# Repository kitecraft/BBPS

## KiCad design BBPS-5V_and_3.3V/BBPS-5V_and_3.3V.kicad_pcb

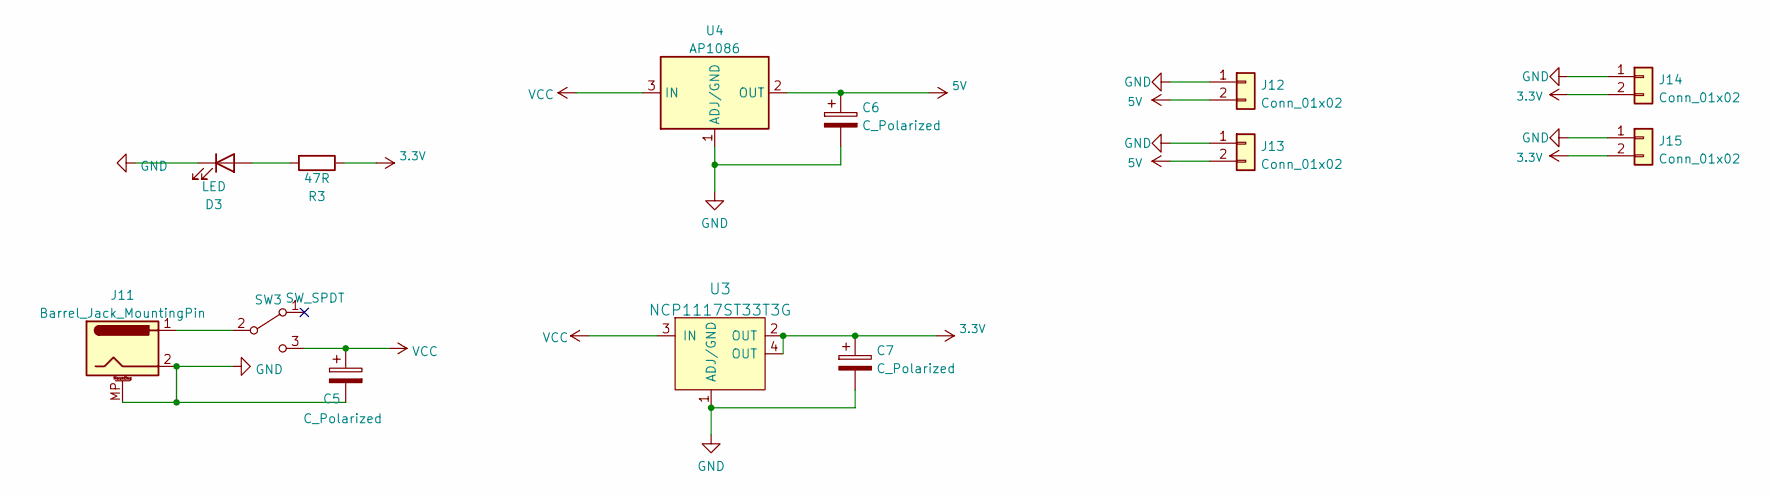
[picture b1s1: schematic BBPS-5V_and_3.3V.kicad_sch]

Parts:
C5: C_Polarized; CP_Elec_6.3x5.9
C6, C7: C_Polarized; C_0805_2012Metric
D3: LED; LED_1206_3216Metric
J11: Barrel_Jack_MountingPin; BarrelJack_CUI_PJ-102AH_Horizontal_3_Pin_Short
J12, J13, J14, J15: Conn_01x02; PinHeader_1x02_P2.54mm_Vertical
R3: 47R; R_1206_3216Metric
SW3: SW_SPDT; SPDT_Switch_3mm
U3: NCP1117ST33T3G; SOT-223; MPN NCP1117ST33T3G; Digi-Key_PN NCP1117ST33T3GOSCT-ND
U4: AP1086; TO-263-2

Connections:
3.3V: C7.1, J14.2, J15.2, R3.1, U3.2 (OUT), U3.4 (OUT)
5V: C6.1, J12.2, J13.2, U4.2 (OUT)
GND: C5.2, C6.2, C7.2, D3.1 (K), J11.2, J11.MP (MountPin), J12.1, J13.1, J14.1, J15.1, U3.1 (ADJ/GND), U4.1 (ADJ/GND)
unnamed: D3.2 (A), R3.2
unnamed: J11.1, SW3.2 (B)
VCC: C5.1, SW3.3 (C), U3.3 (IN), U4.3 (IN)

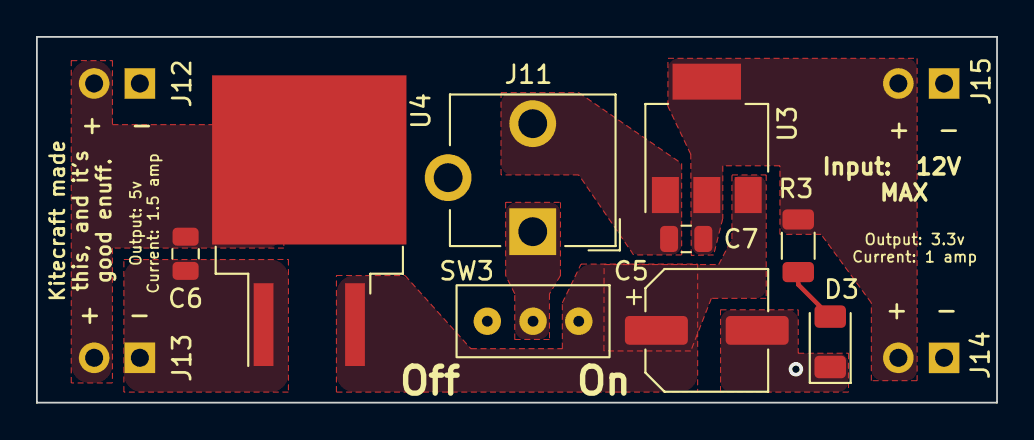
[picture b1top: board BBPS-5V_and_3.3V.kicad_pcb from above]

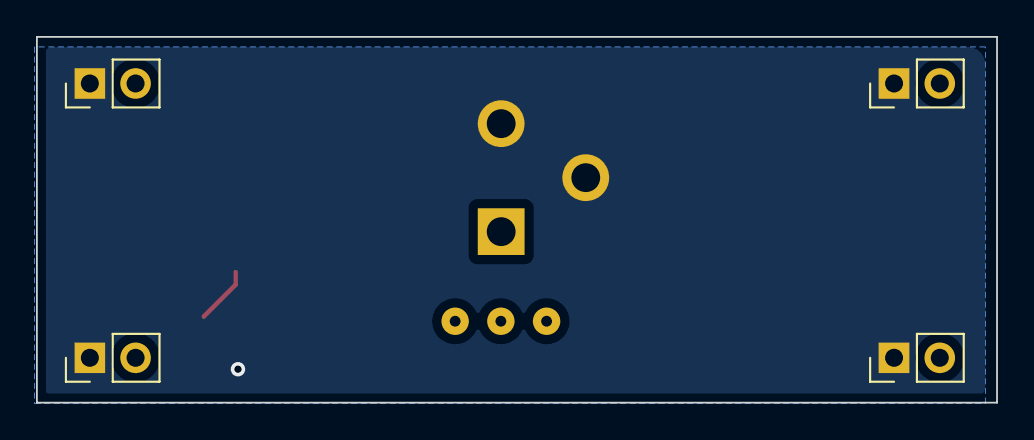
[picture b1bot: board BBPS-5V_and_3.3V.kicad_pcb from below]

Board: 2 copper layers, 53.3 x 20.3 mm, 13 parts (4 on the bottom side), 6 nets.

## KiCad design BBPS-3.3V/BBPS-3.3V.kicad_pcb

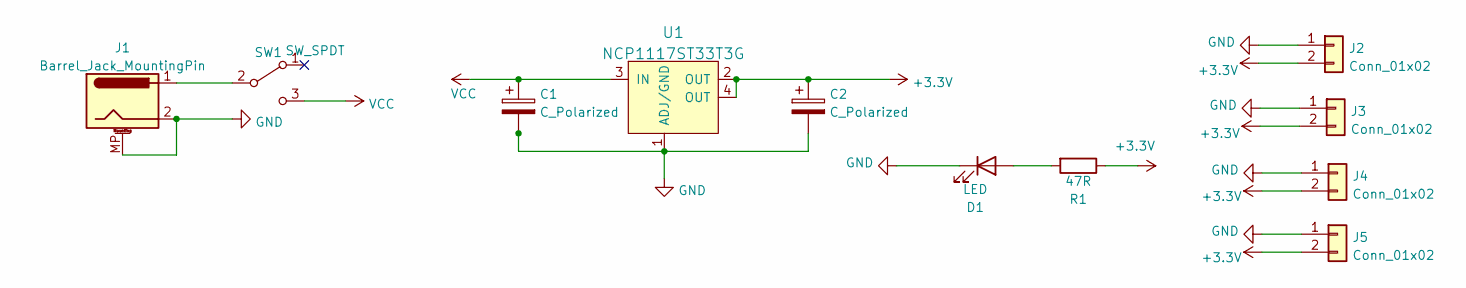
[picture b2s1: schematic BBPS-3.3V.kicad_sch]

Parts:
C1: C_Polarized; CP_Elec_6.3x5.9
C2: C_Polarized; C_0805_2012Metric
D1: LED; LED_1206_3216Metric
J1: Barrel_Jack_MountingPin; BarrelJack_CUI_PJ-102AH_Horizontal_3_Pin_Short
J2, J3, J4, J5: Conn_01x02; PinHeader_1x02_P2.54mm_Vertical
R1: 47R; R_1206_3216Metric
SW1: SW_SPDT; SPDT_Switch_3mm
U1: NCP1117ST33T3G; SOT-223; MPN NCP1117ST33T3G; Digi-Key_PN NCP1117ST33T3GOSCT-ND

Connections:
+3V3: C2.1, J2.2, J3.2, J4.2, J5.2, R1.1, U1.2 (OUT), U1.4 (OUT)
GND: C1.2, C2.2, D1.1 (K), J1.2, J1.MP (MountPin), J2.1, J3.1, J4.1, J5.1, U1.1 (ADJ/GND)
unnamed: D1.2 (A), R1.2
unnamed: J1.1, SW1.2 (B)
VCC: C1.1, SW1.3 (C), U1.3 (IN)

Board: 2 copper layers, 11 parts (4 on the bottom side), 5 nets, no tracks yet.

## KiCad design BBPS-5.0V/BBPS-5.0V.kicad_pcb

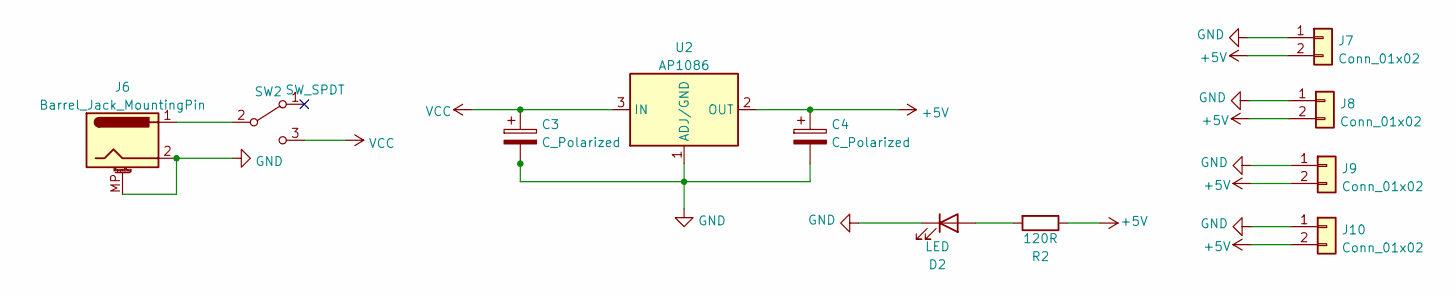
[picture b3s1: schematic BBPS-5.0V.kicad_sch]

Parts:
C3: C_Polarized; CP_Elec_6.3x5.9
C4: C_Polarized; C_0805_2012Metric
D2: LED; LED_1206_3216Metric
J6: Barrel_Jack_MountingPin; BarrelJack_CUI_PJ-102AH_Horizontal_3_Pin_Short
J7, J8, J9, J10: Conn_01x02; PinHeader_1x02_P2.54mm_Vertical
R2: 120R; R_1206_3216Metric
SW2: SW_SPDT; SPDT_Switch_3mm
U2: AP1086; TO-263-2

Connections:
+5V: C4.1, J7.2, J8.2, J9.2, J10.2, R2.1, U2.2 (OUT)
GND: C3.2, C4.2, D2.1 (K), J6.2, J6.MP (MountPin), J7.1, J8.1, J9.1, J10.1, U2.1 (ADJ/GND)
unnamed: D2.2 (A), R2.2
unnamed: J6.1, SW2.2 (B)
VCC: C3.1, SW2.3 (C), U2.3 (IN)

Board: 2 copper layers, 11 parts (4 on the bottom side), 5 nets, no tracks yet.

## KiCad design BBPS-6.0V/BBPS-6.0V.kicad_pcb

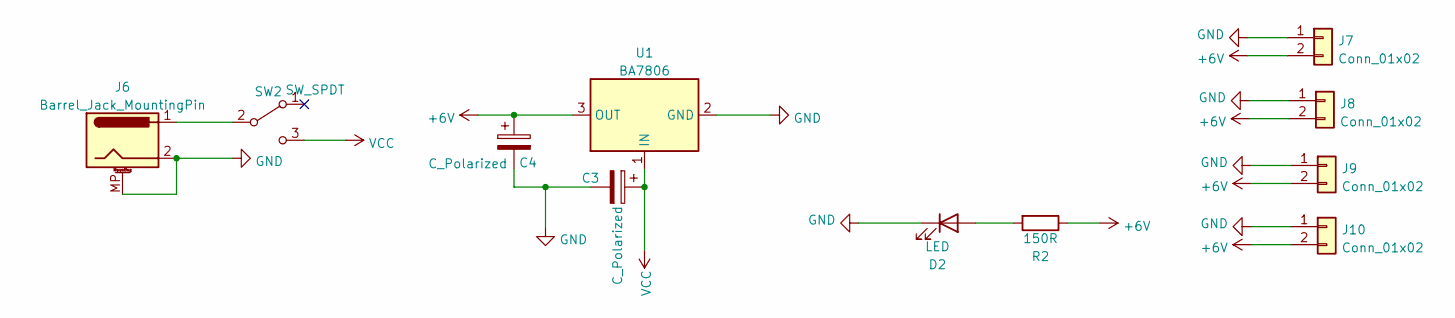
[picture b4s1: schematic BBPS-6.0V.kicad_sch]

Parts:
C3: C_Polarized; CP_Elec_6.3x5.9
C4: C_Polarized; C_0805_2012Metric
D2: LED; LED_1206_3216Metric
J6: Barrel_Jack_MountingPin; BarrelJack_CUI_PJ-102AH_Horizontal_3_Pin_Short
J7, J8, J9, J10: Conn_01x02; PinHeader_1x02_P2.54mm_Vertical
R2: 150R; R_1206_3216Metric
SW2: SW_SPDT; SPDT_Switch_3mm
U1: BA7806; TO-252-2

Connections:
+6V: C4.1, J7.2, J8.2, J9.2, J10.2, R2.1, U1.3 (OUT)
GND: C3.2, C4.2, D2.1 (K), J6.2, J6.MP (MountPin), J7.1, J8.1, J9.1, J10.1, U1.2 (GND)
unnamed: D2.2 (A), R2.2
unnamed: J6.1, SW2.2 (B)
VCC: C3.1, SW2.3 (C), U1.1 (IN)

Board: 2 copper layers, 11 parts (4 on the bottom side), 5 nets, no tracks yet.

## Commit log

2022-09-16 4 Bread board power supplies. 3.3v 5v, 3.3v & 5v, 6v
